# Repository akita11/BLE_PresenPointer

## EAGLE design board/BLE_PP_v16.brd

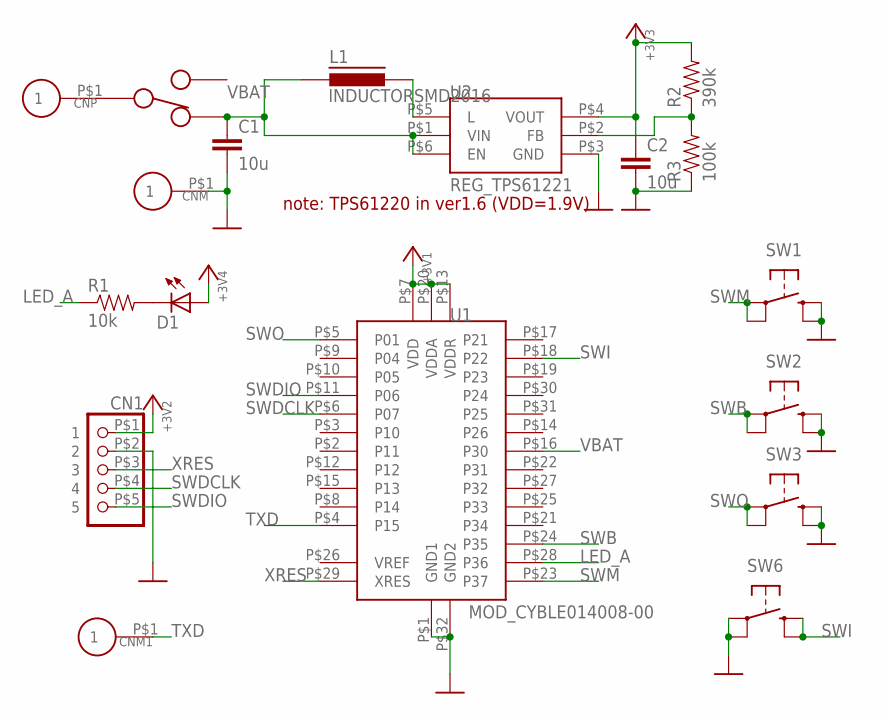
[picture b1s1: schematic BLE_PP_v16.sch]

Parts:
C1, C2: 10u; 0603
CN1: CON_PINHD-1X550MIL; 1X5_50MIL
CNM, CNM1: CON_P01SMD1MM; PAD_SMD1MM
CNP: CON_P01SMD1MM; PAD_SMD1MM
D1: LED0603; SPARKFUN_LED-0603
L1: INDUCTORSMD2016; 2016
R1: 10k; 0603
R2: 390k; 0603
R3: 100k; 0603
SW1: SW_TACTEVQP2; SW_EVQP2
SW2, SW3: SW_TACTEVQPLNA08NOGND; SW_EVQPLBA08_NOGND
SW4: SW_SLIDECUS12B; SW_CUS-12B
SW6: SW_TACTEVQP7; SW_EVQP7
U1: MOD_CYBLE014008-00
U2: REG_TPS61221; SC70-6

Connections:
+3V3: C2.1, CN1.P$1 (1), D1.A, R2.2, U1.P$7 (VDD), U1.P$13 (VDDR), U1.P$20 (VDDA), U2.P$4 (VOUT)
GND: C1.2, C2.2, CN1.P$2 (2), CNM.P$1, R3.1, SW1.PB1 (S), SW1.PB2 (S1), SW2.B1 (S), SW2.B2 (S1), SW3.B1 (S), SW3.B2 (S1), SW6.P$1A, SW6.P$1B (P1), U1.P$1 (GND1), U1.P$32 (GND2), U2.P$3 (GND)
LED_A: R1.1, U1.P$28 (P36)
unnamed: R2.1, R3.2, U2.P$2 (FB)
unnamed: L1.P$2 (2), U2.P$5 (L)
unnamed: D1.C, R1.2
unnamed: CNP.P$1, SW4.P$2
P$3: SW4.P$3
SWB: SW2.A1, SW2.A2 (P1), U1.P$24 (P35)
SWDCLK: CN1.P$4 (4), U1.P$6 (P07)
SWDIO: CN1.P$5 (5), U1.P$11 (P06)
SWI: SW6.P$2A (S), SW6.P$2B (S1), U1.P$18 (P22)
SWM: SW1.PA1, SW1.PA2 (P1), U1.P$23 (P37)
SWO: SW3.A1, SW3.A2 (P1), U1.P$5 (P01)
TXD: CNM1.P$1, U1.P$4 (P15)
VBAT: C1.1, L1.P$1 (1), SW4.P$1, U1.P$16 (P30), U2.P$1 (VIN), U2.P$6 (EN)
XRES: CN1.P$3 (3), U1.P$29 (XRES)

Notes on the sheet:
note: TPS61220 in ver1.6 (VDD=1.9V)

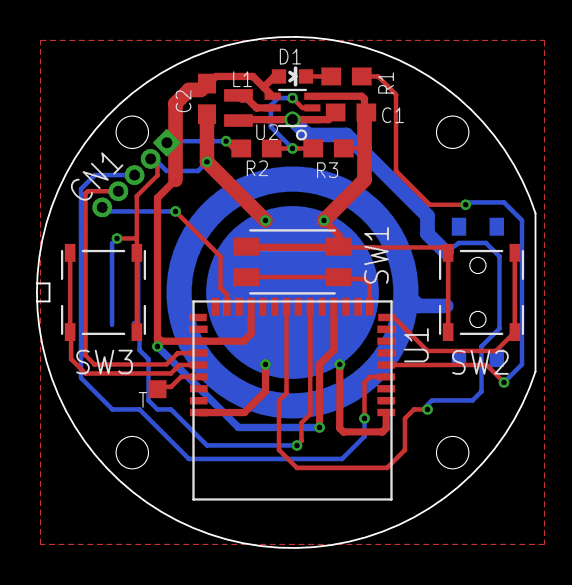
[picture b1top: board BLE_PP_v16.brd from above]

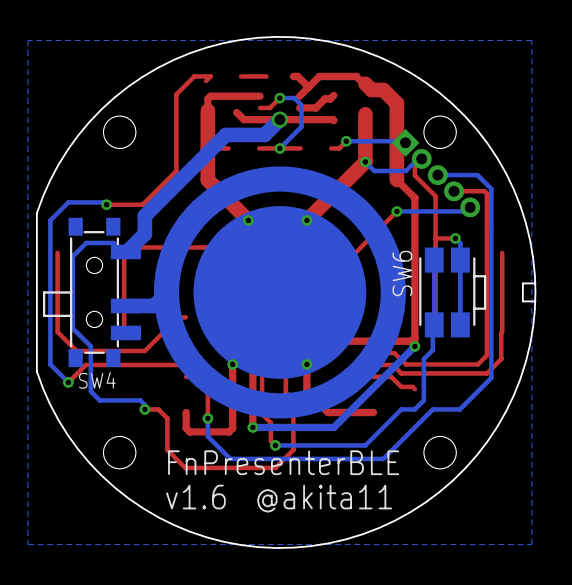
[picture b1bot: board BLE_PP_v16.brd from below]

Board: 2 copper layers, 27.7 x 28.4 mm, 18 parts (4 on the bottom side), 16 nets.

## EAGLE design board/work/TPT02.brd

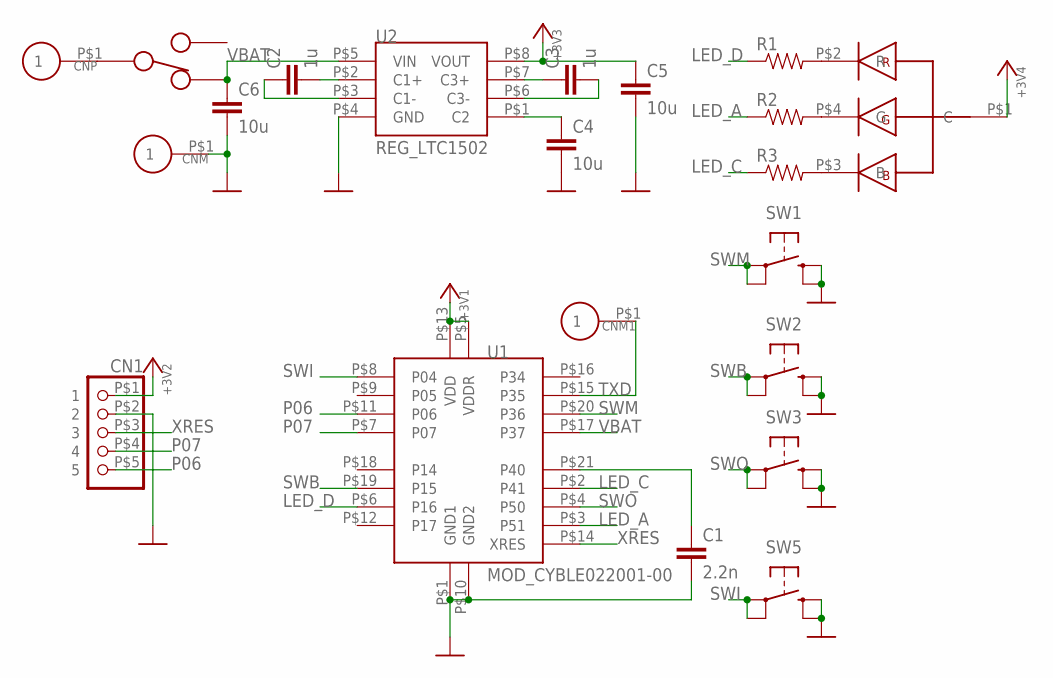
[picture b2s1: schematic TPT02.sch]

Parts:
C1: 2.2n; 0603
C2, C3: 1u; 0603
C4, C5, C6: 10u; 0603
CN1: CON_PINHD-1X550MIL; 1X5_50MIL
CNM, CNM1: CON_P01SMD1MM; PAD_SMD1MM
CNP: CON_P01SMD1MM; PAD_SMD1MM
D1: LED_RGB_OSTB0603C1C; LED_0606_4P
R1, R2, R3: RES0603; 0603
SW1: SW_TACTEVQP2; SW_EVQP2
SW2, SW3: SW_TACTPTS525SK08; SW_PTS525SK08
SW4: SW_SLIDECUS12; SW_CUS-12B
SW5: SW_TACTEVQPU02; SW_EVQPUA02
U1: MOD_CYBLE022001-00
U2: REG_LTC1502; MSOP8

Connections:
+3V3: C5.1, CN1.P$1 (1), D1.P$1 (C), U1.P$5 (VDDR), U1.P$13 (VDD), U2.P$8 (VOUT)
GND: C1.2, C4.2, C5.2, C6.2, CN1.P$2 (2), CNM.P$1, SW1.PB1 (S), SW1.PB2 (S1), SW2.P$B1 (S), SW2.P$B2 (S1), SW3.P$B1 (S), SW3.P$B2 (S1), SW5.PB1 (S), SW5.PB2 (S1), U1.P$1 (GND1), U1.P$10 (GND2), U2.P$4 (GND)
LED_A: R2.1, U1.P$3 (P51)
LED_C: R3.1, U1.P$2 (P41)
LED_D: R1.1, U1.P$6 (P16)
unnamed: C1.1, U1.P$21 (P40)
unnamed: C4.1, U2.P$1 (C2)
unnamed: C2.2, U2.P$2 (C1+)
unnamed: C2.1, U2.P$3 (C1-)
unnamed: C3.1, U2.P$7 (C3+)
unnamed: C3.2, U2.P$6 (C3-)
unnamed: CNP.P$1, SW4.P$2
unnamed: D1.P$2 (R), R1.2
unnamed: D1.P$4 (G), R2.2
unnamed: D1.P$3 (B), R3.2
P06: CN1.P$5 (5), U1.P$11 (P06)
P07: CN1.P$4 (4), U1.P$7 (P07)
P$3: SW4.P$3
SWB: SW2.P$A1, SW2.P$A2 (P1), U1.P$19 (P15)
SWI: SW5.PA1, SW5.PA2 (P1), U1.P$8 (P04)
SWM: SW1.PA1, SW1.PA2 (P1), U1.P$20 (P36)
SWO: SW3.P$A1, SW3.P$A2 (P1), U1.P$4 (P50)
TXD: CNM1.P$1, U1.P$15 (P35)
VBAT: C6.1, SW4.P$1, U1.P$17 (P37), U2.P$5 (VIN)
XRES: CN1.P$3 (3), U1.P$14 (XRES)

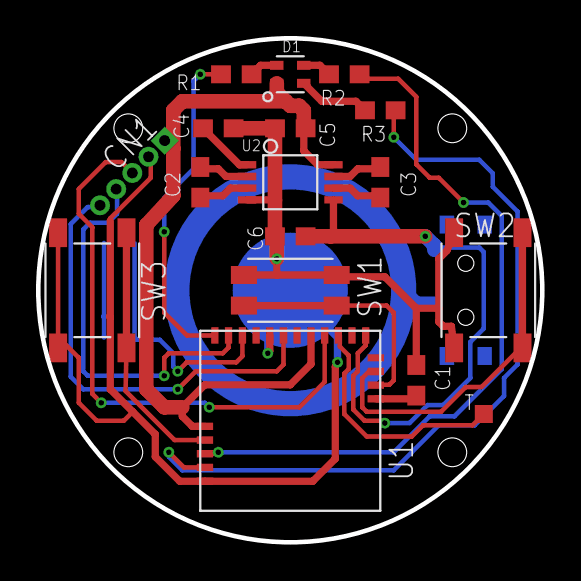
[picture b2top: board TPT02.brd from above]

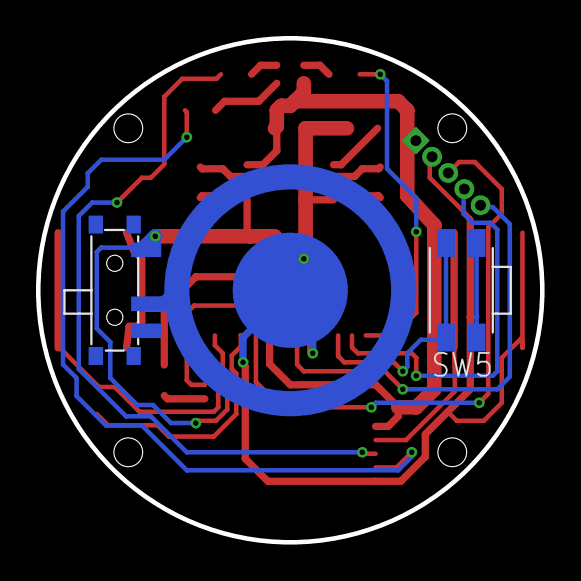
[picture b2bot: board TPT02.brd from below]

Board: 2 copper layers, 28.0 x 28.0 mm, 21 parts (4 on the bottom side), 24 nets.

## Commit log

2016-12-22 modified switch handling based on original HID-Keyboard sample
2016-12-22 スイッチの扱いをHID-Keyboardサンプルにならって修正。基板でバッテリ電圧を測定できるように修正。
2016-12-23 基板の修正（バッテリ電圧計測＆TXD端子）
2016-12-23 両脇のスイッチ(SWB/SWO)のパッケージを変更
2016-12-26 CYBLE014008 version (TPT02r) board & source
2017-01-04 電源をブーストDC/DCに変更。スイッチサイズ、基板サイズの調整。
2017-01-04 Cの部品番号を整理。Elecrow向けBOMを作成。
2017-01-08 部品の位置の微調整。
2017-01-10 両側のタクトスイッチのGND端子が基板端にかかるため削除
2017-01-19 表面ソルダーマスクの追加
2017-01-29 部品位置の微調整。ソースの微調整（コネクト時にLED点滅）。
2017-01-30 基板外径・シルクの微調整
2017-01-30 バッテリレベルを通知しないように変更。
2017-01-30 バッテリ情報を通知しないように変更。
2017-02-05 TELEC認証に関するファイルの追加。
2017-02-20 無操作10分でhibernate、ボタン操作時にLEDフラッシュ。
2017-02-23 Stopからでも復帰できるようにIDスイッチをP2.2に接続
2017-02-27 BLEモジュールのハンダマスクを少し小さく修正
2017-04-11 ファイルの整理、readmeの追加、組み立てマニュアルの追加
2017-04-11 ファイルの整理
2017-04-14 マニュアルの追記
2017-04-15 マニュアルの修正(消費電流についての記述を追加）
2017-04-15 マニュアル（製品同梱ダイジェスト版）の追加
2017-04-16 ConnectionIntervalの最小・最大値を変更(7.5/15→30/60)。履歴基板データの整理。マニュアルの消費電流記述の変更。
2017-04-19 ソースコードの修正（消費電力低減）、それにともなうマニュアルの修正。
2017-04-19 ソースコード修正（スリープ時間を30分に、キーコードをPageUp/Downに）。マニュアルの修正。
2017-04-21 スリープに入るアルゴリズム＆L2CAP paramUpdateRequestを送るアルゴリズムを変更。SleepからIDボタンで復帰。マニュアルの修正。
2017-04-21 ソースコードの調整
2017-04-24 v1.6のBOMを追加
